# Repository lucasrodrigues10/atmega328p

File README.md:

# Optimus Prime v2.0 #

Este projeto é um de robô realizado para o trabalho de microcontroladores de Engenharia de Computação do Instituto Mauá de Tecnologia sob orientação do Tiago Sanches da Silva (qualquer reclamação pode contactá-lo e elogios falar com os integrantes). 

## Componentes
 - **ATmega328P-PU**
 - **USBasp**
 - **HC-SR04**
 - **2x Motor DC**
 - **DRIVER PONTE H L298N**
 - **Botão**

## Integrantes do Grupo
* **Lucas de Moura Rodrigues** - *14.00556-5*
* **Levon Tcholakian Chahestian** - *14.01587-0*
* **Raul Freitas Vaz** - *14.03065-9*
* **Yurão** - *14.xxxxx-x*

## Configuração para Desenvolvimento 
* Configurar Atmel Studio - https://www.youtube.com/watch?v=qD5EP8tgVpY
* Sensor Ultrassonico - https://www.youtube.com/watch?v=DZJoDpMBPEw

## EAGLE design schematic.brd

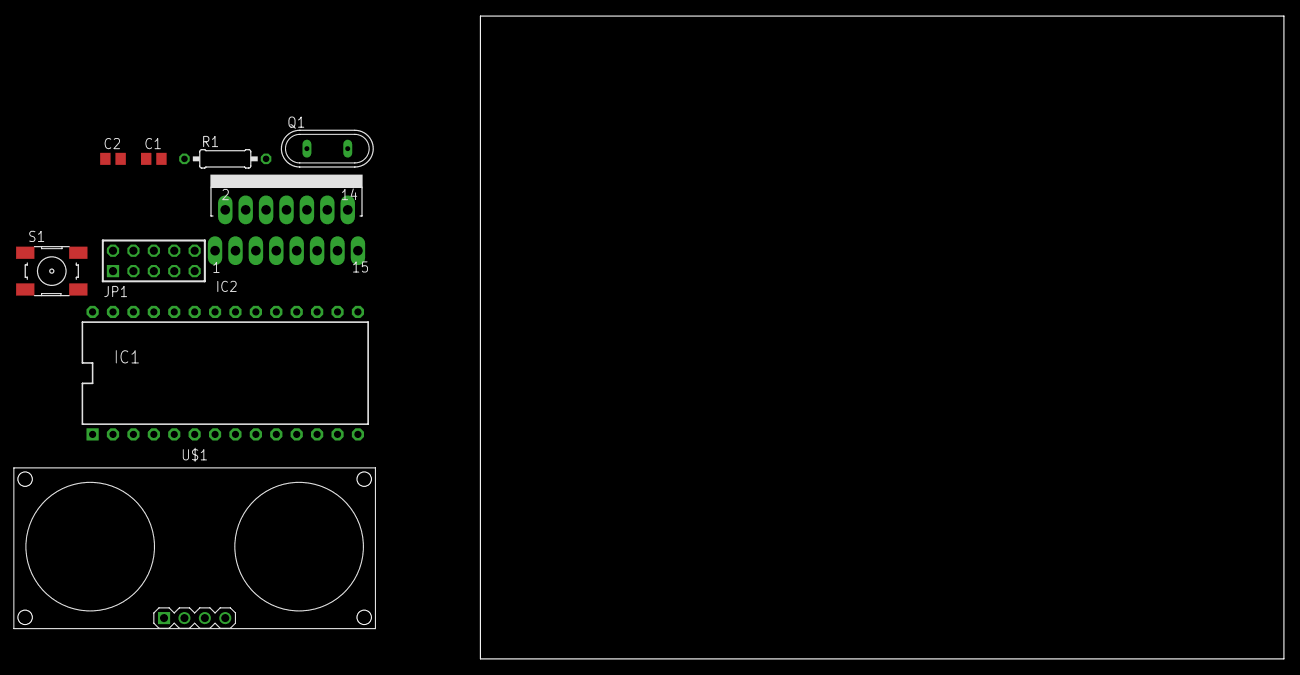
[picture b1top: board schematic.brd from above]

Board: 2 copper layers, 100.0 x 80.0 mm, 9 parts (0 on the bottom side), 6 nets, no tracks yet.

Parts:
C1, C2: C0805
IC1: DIL28
IC2: L298; MULTIWATT-15
JP1: AVR-ISP-10
Q1: QS
R1: 0207/10
S1: 6MM_SWITCH
U$1: ULTRASONIC-HC-SR04

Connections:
GND: IC1.8, IC1.22, IC2.8, U$1.4
unnamed: IC1.17, JP1.1
unnamed: IC1.18, JP1.9
unnamed: IC1.19, JP1.7
unnamed: IC1.1, JP1.5
VCC: IC2.9, JP1.2, U$1.1

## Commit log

2017-10-19 Adicionando um projeto simples de blink
2017-10-19 Adicionado interrupcao
2017-10-20 Adicionado mais comentarios e um projeto com interrupcao
2017-10-20 Adicionei o datasheet e pinos
2017-10-20 Adicionado pinos no readme
2017-10-21 Criado projeto timer falta modificacoes
2017-10-22 Adicionei pisca led
2017-10-22 Melhorado timer operacao normal
2017-10-22 Adicionado timer ctc
2017-10-22 Fast pwm add
2017-10-22 PWM Fast Melhorado
2017-10-24 Adicionamos a segunda roda e seno
2017-10-31 UART
2017-11-09 Projeto reformulado e documentado
2017-11-09 removi arquivos desnecessarios
2017-11-09 Adicionei projeto do sensor ultrassonico
2017-11-09 Projetos de sonar adicionados
2017-11-10 Sensor funciona lisinho
2017-11-11 Software pronto!
2017-11-12 Adicionado botao para pegar dados
    Hardware esta a atrapalhar
2017-11-12 Adicionado botao para pegar dados
    Hardware esta atrapalhando
2017-11-17 Adicionei o esquematico
2017-11-17 adicionei pinos imagem
2017-11-18 Atualizei esquematico
2017-11-29 Adicionado OCR0B para controlador
2017-12-04 Robo acha objeto mais proximo e bate nele

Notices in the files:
parts and their libraries:
diy-modules: Released under the Creative Commons Attribution 4.0 International License: http://creativecommons.org/licenses/by/4.0
